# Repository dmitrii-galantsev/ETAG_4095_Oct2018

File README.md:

# ETAG is an RFID reader board used for academic research

Please refer to [Wiki](https://github.com/dmitrii-galantsev/ETAG_Rosvall/wiki) for additional information.

Download files from here [https://github.com/dmitrii-galantsev/ETAG_Rosvall/wiki/Download-Firmware](https://github.com/dmitrii-galantsev/ETAG_Rosvall/wiki/Download-Firmware)

Stable branch: [v1.3](https://github.com/dmitrii-galantsev/ETAG_Rosvall/tree/v1.3)

```
___________________________    ________          .---.        .-----------
\_   _____/\__    ___/  _  \  /  _____/         /     \  __  /    ------
 |    __)_   |    | /  /_\  \/   \  ___        / /     \(  )/    -----
 |        \  |    |/    |    \    \_\  \      //////   ' \/ `   ---
/_______  /  |____|\____|__  /\______  /     //// / // :    : ---
        \/                 \/        \/     // /   /  /`    '--
                                           //          //..\\
                                                  ====UU====UU====
                                                      '//||\\`
                                                         ''``
version: master

Hardware was not created by me, nor were the original files.
Original firmware belongs to Eli Bridge and other collaborators.
Eli's repo: https://github.com/Eli-S-Bridge/ETAG_4095_Oct2018

All work is Licensed in the public domain.

This is a fork highly specialized for Rosvall Lab usage in Indiana University, Bloomington.

*** Directories ***
./ETAG_Rosvall	- Arduino source files. Compile from here.
./board_files	- Board schematics and arduino board file
./images		- Images for the Wiki
./pdfs			- Additional documentation

*** Measurements ***
Date: 	01/08/2018
Power:	Laptop
Commit: 262f8f9e11d535dba44aab24ae57a1ed34d76e22
Comment: these values are strictly for testing and might differ in the field
Stand-by:
	-> 22-35 mA
RFID scanned:
	-> ~40-60 mA
Sleep:
	-> 8.2 mA
```

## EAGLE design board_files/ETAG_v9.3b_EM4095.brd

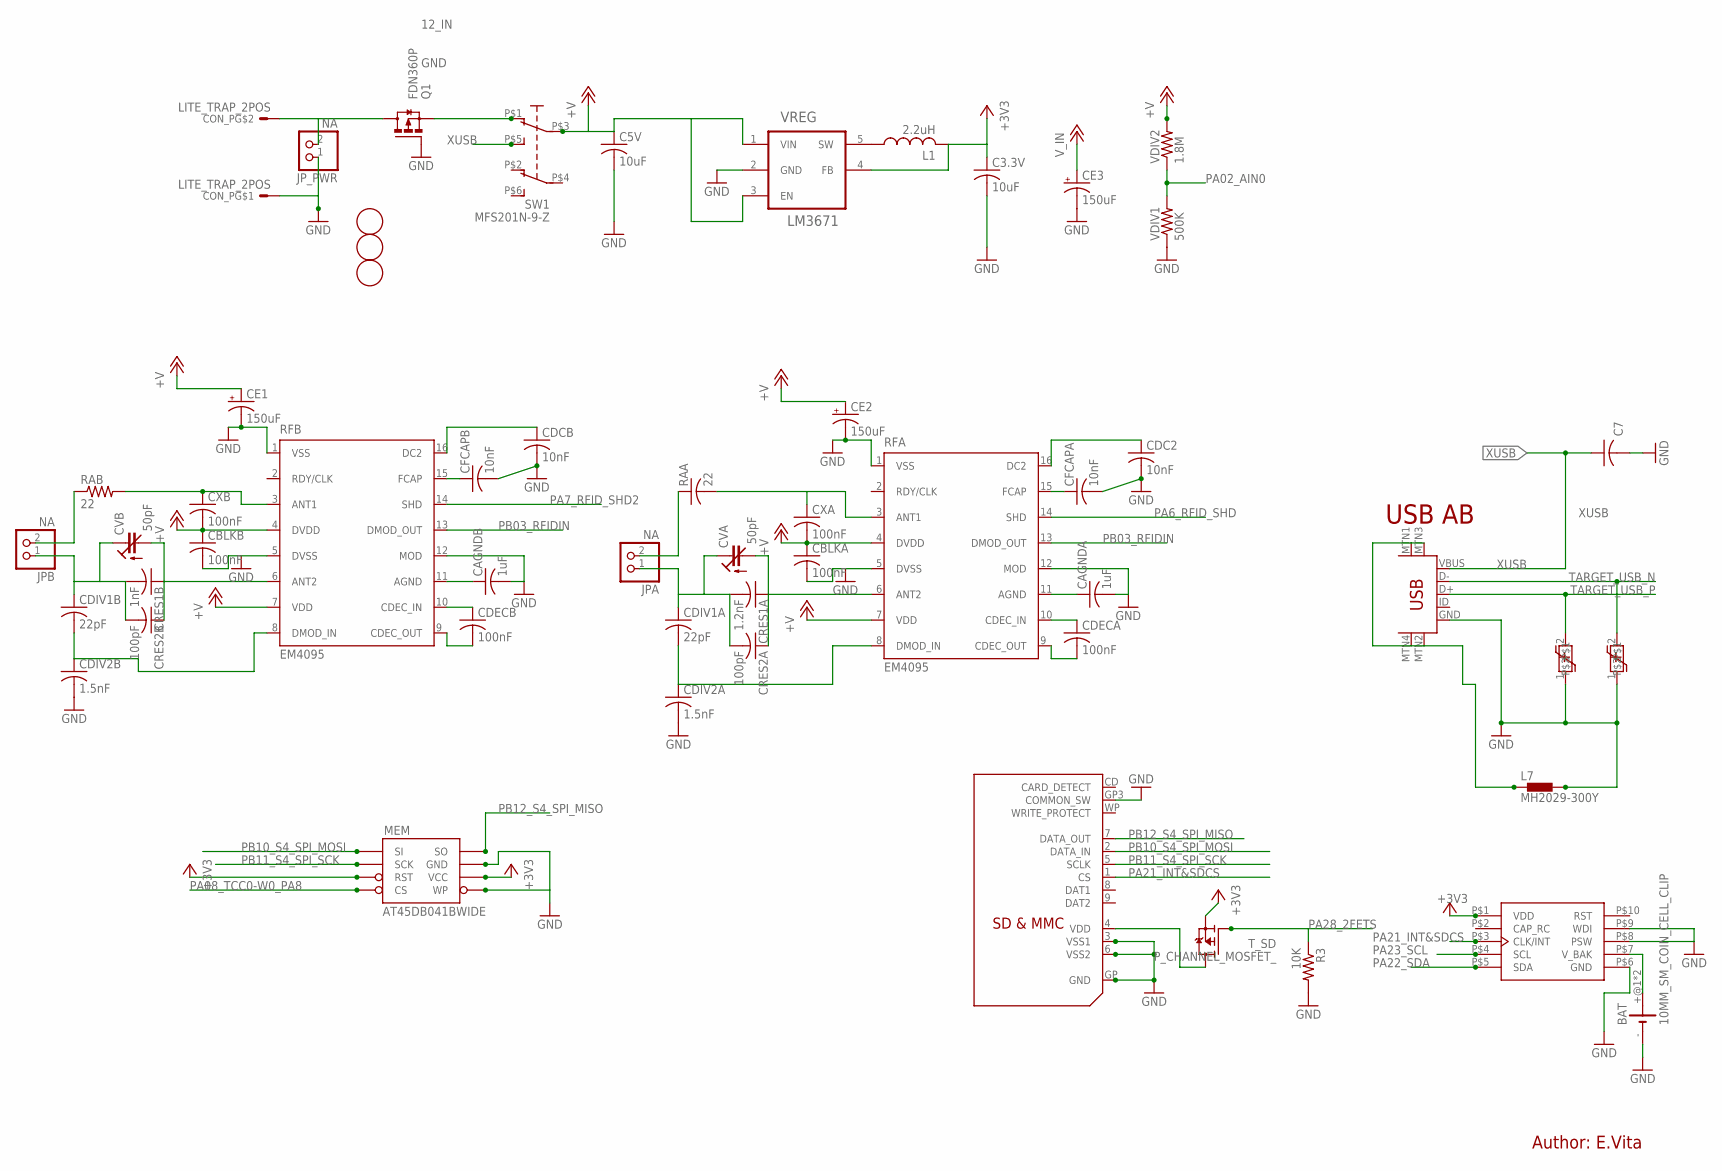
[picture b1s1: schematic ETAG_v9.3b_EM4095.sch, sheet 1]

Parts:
BAT: 10MM_SM_COIN_CELL_CLIP
C3.3V, C5V: 10uF; C0805
C7: 10nF; C0603-ROUND
CAGNDA: 1uF; C0603-ROUND
CAGNDB: 1uF; C0603-ROUND
CBLKA: 100nF; C0603-ROUND
CBLKB: 100nF; C0603-ROUND
CDC2: 10nF; C0603-ROUND
CDCB: 10nF; C0603-ROUND
CDECA: 100nF; C0603-ROUND
CDECB: 100nF; C0603-ROUND
CDIV1A, CDIV1B: 22pF; C0603-ROUND
CDIV2A, CDIV2B: 1.5nF; C0603-ROUND
CE1, CE2, CE3: 150uF; E2-5
CFCAPA: 10nF; C0603-ROUND
CFCAPB: 10nF; C0603-ROUND
CON_P: LITE_TRAP_2POS; LITE_TRAP_MINI
CRES1A: 1.2nF; C0603-ROUND
CRES1B: 1nF; C0603-ROUND
CRES2A, CRES2B: 100pF; C0603-ROUND
CVA: 50pF; CTRIM3018_11
CVB: 50pF; CTRIM3018_11
CXA: 100nF; C0603-ROUND
CXB: 100nF; C0603-ROUND
FD1, FD2, FD3: FIDUCIALMOUNT; FIDUCIA-MOUNT
JPA: NA; 1X02
JPB: NA; 1X02
JP_PWR: NA; 1X02
L1: 2.2uH; SMT_COIL_INDUCTOR_4X4MM
L7: MH2029-300Y; C0805K
MEM: AT45DB041BWIDE; SO08WIDE
Q1: FDN360P; SUPER-SOT3
R3: 10K; C0603-ROUND
RAA: 22; C0805
RAB: 22; R0805
RFA: EM4095; SO16
RFB: EM4095; SO16
RTC: MC-RTC-RV-1805-C3-I2C; MC-RTC-C3
SD: SDMMC06132; 06132
SW1: MFS201N-9-Z
T_SD: P_CHANNEL_MOSFET_; SOT23
USB: USB-MINIB-5PIN; USB-MINIB
VDIV1: 500K; C0603-ROUND
VDIV2: 1.8M; C0603-ROUND
VREG: LM3671; SOT23-5L
Z5, Z6: ESD_SUPRESSOR; C0603-ROUND

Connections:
2GND: L7.1, USB.MTN1 (MTN2), USB.MTN2 (MTN3), USB.MTN3 (MTN1), USB.MTN4
12_IN: CON_P.P$3, CON_P.P$4, JP_PWR.2, Q1.3 (D)
+3V3: C3.3V.1, L1.P$2 (2), MEM.3 (RST), MEM.6 (VCC), RTC.P$1 (VDD), T_SD.2 (S), VREG.4 (FB); also elsewhere on the board
CVB: CDIV1B.1, CRES1B.2, CRES2B.2, CVB.+ (E), JPB.1
GND: BAT.-, C3.3V.2, C5V.2, C7.2, CAGNDA.2, CAGNDB.2, CBLKA.2, CBLKB.2, CDC2.2, CDCB.2, CDIV2A.2, CDIV2B.2, CE1.-, CE2.-, CE3.-, CFCAPA.2, CFCAPB.2, CON_P.P$1, CON_P.P$2, JP_PWR.1, L7.2, MEM.5 (WP), MEM.7 (GND), Q1.1 (G), R3.2, RFA.1 (VSS), RFA.5 (DVSS), RFA.12 (MOD), RFB.1 (VSS), RFB.5 (DVSS), RFB.12 (MOD), RTC.P$6 (GND), RTC.P$8 (PSW), RTC.P$9 (WDI), SD.3 (VSS1), SD.6 (VSS2), SD.GP (GND), SD.GP3 (COMMON_SW), USB.GND, VDIV1.1, VREG.2 (GND), Z5.1, Z6.1; also elsewhere on the board
unnamed: CFCAPB.1, RFB.15 (FCAP)
unnamed: CAGNDB.1, RFB.11 (AGND)
unnamed: CFCAPA.1, RFA.15 (FCAP)
unnamed: CAGNDA.1, RFA.11 (AGND)
unnamed: CDC2.1, RFA.16 (DC2)
unnamed: CRES1B.1, CRES2B.1, CVB.- (A), RFB.6 (ANT2)
unnamed: CDIV1B.2, CDIV2B.1, RFB.8 (DMOD_IN)
unnamed: CDCB.1, RFB.16 (DC2)
unnamed: CDECB.2, RFB.9 (CDEC_OUT)
unnamed: CRES1A.1, CRES2A.1, CVA.- (A), RFA.6 (ANT2)
unnamed: CDIV1A.2, CDIV2A.1, RFA.8 (DMOD_IN)
unnamed: CDIV1A.1, CRES1A.2, CRES2A.2, CVA.+ (E), JPA.1
unnamed: CDECB.1, RFB.10 (CDEC_IN)
unnamed: CXB.1, RAB.2, RFB.3 (ANT1)
unnamed: Q1.2 (S), SW1.P$1 (O)
unnamed: CDECA.2, RFA.9 (CDEC_OUT)
unnamed: CDECA.1, RFA.10 (CDEC_IN)
unnamed: CXA.1, RAA.2, RFA.3 (ANT1)
unnamed: JPB.2, RAB.1
unnamed: JPA.2, RAA.1
PA02_AIN0: VDIV1.2, VDIV2.1; also elsewhere on the board
PA6_RFID_SHD: RFA.14 (SHD); also elsewhere on the board
PA7_RFID_SHD2: RFB.14 (SHD); also elsewhere on the board
PA08_TCC0-W0_PA8: MEM.4 (CS); also elsewhere on the board
PA21_INT&SDCS: RTC.P$3 (CLK/INT), SD.1 (CS); also elsewhere on the board
PA22_SDA: RTC.P$5 (SDA); also elsewhere on the board
PA23_SCL: RTC.P$4 (SCL); also elsewhere on the board
PA28_2FETS: R3.1, T_SD.1 (G); also elsewhere on the board
PB03_RFIDIN: RFA.13 (DMOD_OUT), RFB.13 (DMOD_OUT); also elsewhere on the board
PB10_S4_SPI_MOSI: MEM.1 (SI), SD.2 (DATA_IN); also elsewhere on the board
PB11_S4_SPI_SCK: MEM.2 (SCK), SD.5 (SCLK); also elsewhere on the board
PB12_S4_SPI_MISO: MEM.8 (SO), SD.7 (DATA_OUT); also elsewhere on the board
SW: L1.P$1 (1), VREG.5 (SW)
TARGET_USB_N: USB.D-, Z6.2; also elsewhere on the board
TARGET_USB_P: USB.D+, Z5.2; also elsewhere on the board
VBAT1: BAT.+@1 (+), BAT.+@2 (+), RTC.P$7 (V_BAK)
VDD: SD.4 (VDD), T_SD.3 (D)
V_IN: C5V.1, CBLKA.1, CBLKB.1, CE1.+, CE2.+, CE3.+, CXA.2, CXB.2, RFA.4 (DVDD), RFA.7 (VDD), RFB.4 (DVDD), RFB.7 (VDD), SW1.P$3, VDIV2.2, VREG.1 (VIN), VREG.3 (EN); also elsewhere on the board
XUSB: C7.1, SW1.P$5 (S), USB.VBUS

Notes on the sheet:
USB AB
Author: E.Vita

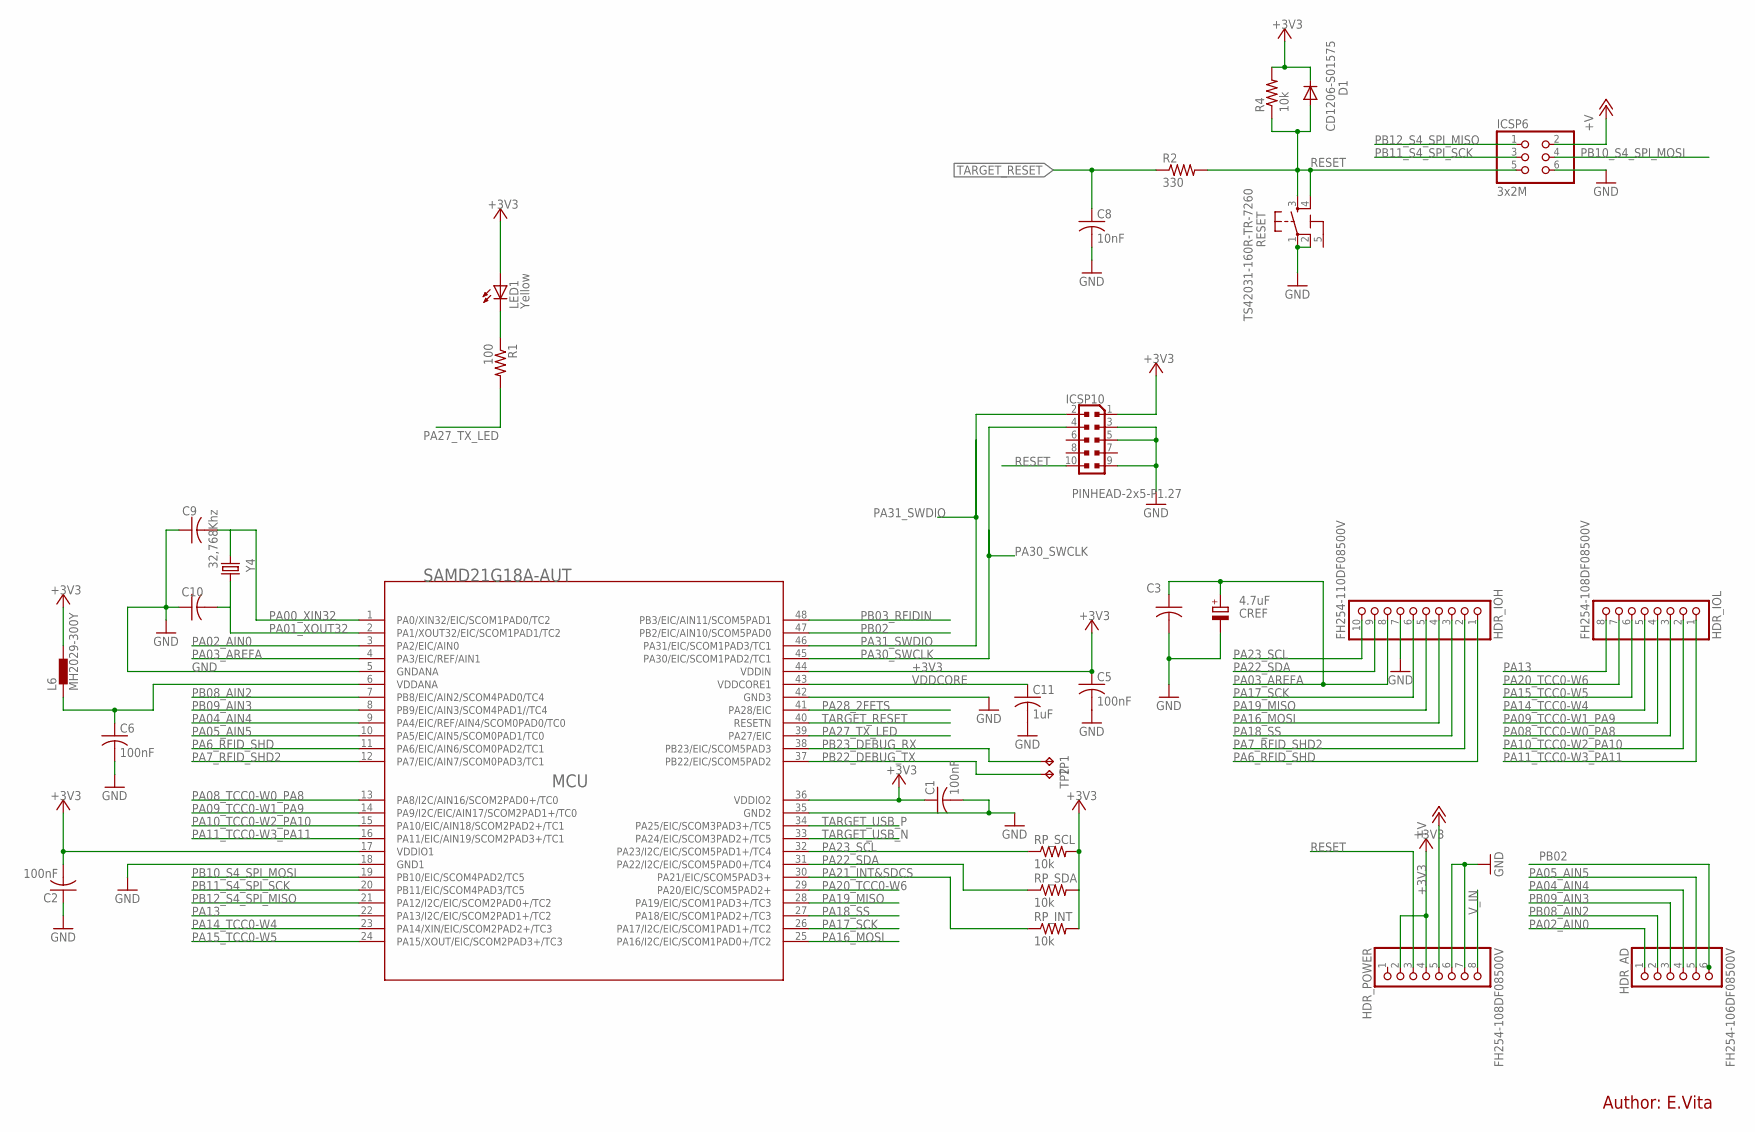
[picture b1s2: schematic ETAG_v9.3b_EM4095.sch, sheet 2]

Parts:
C1, C2, C3, C5, C6: 100nF; C0603-ROUND
C8: 10nF; C0603-ROUND
C9, C10: 22pF; C0603-ROUND
C11: 1uF; C0603-ROUND
CREF: 4.7uF; SMC_A
D1: CD1206-S01575; MINIMELF
HDR_AD: FH254-106DF08500V; 1X06
HDR_IOH: FH254-110DF08500V; 1X10
HDR_IOL: FH254-108DF08500V; 1X08
HDR_POWER: FH254-108DF08500V; 1X08
ICSP6: 3x2M; 2X03
ICSP10: PINHEAD-2x5-P1.27; PINHEAD_2X05_127
L6: MH2029-300Y; C0805K
LED1: Yellow; CHIPLED_0805
MCU: SAMD21G18A-AUT; TQFP48-7X7
R1: 100; C0603-ROUND
R2: 330; C0603-ROUND
R4: 10k; C0603-ROUND
RESET: TS42031-160R-TR-7260; TS42
RP_INT: 10k; C0603-ROUND
RP_SCL: 10k; C0603-ROUND
RP_SDA: 10k; C0603-ROUND
TP1, TP2: TPTP15R; TP15R
Y4: 32,768Khz; RESONATOR_EPSON_FC_145

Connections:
5-GND: RESET.5 (5-GND)
+3V3: C1.1, C2.2, C5.1, D1.C, HDR_POWER.2, HDR_POWER.4, ICSP10.1, L6.2, LED1.A, MCU.17 (VDDIO1), MCU.36 (VDDIO2), MCU.44 (VDDIN), R4.2, RP_INT.2, RP_SCL.2, RP_SDA.2; also elsewhere on the board
GND: C1.2, C2.1, C3.2, C5.2, C6.2, C8.2, C9.1, C10.1, C11.2, CREF.-, HDR_IOH.7, HDR_POWER.6, HDR_POWER.7, ICSP6.6, ICSP10.3, ICSP10.5, ICSP10.9, MCU.5 (GNDANA), MCU.18 (GND1), MCU.35 (GND2), MCU.42 (GND3), RESET.1, RESET.2; also elsewhere on the board
unnamed: LED1.C, R1.1
unnamed: C6.1, L6.1, MCU.6 (VDDANA)
PA00_XIN32: C9.2, MCU.1 (PA0/XIN32/EIC/SCOM1PAD0/TC2), Y4.P$1 (1)
PA01_XOUT32: C10.2, MCU.2 (PA1/XOUT32/EIC/SCOM1PAD1/TC2), Y4.P$2 (2)
PA02_AIN0: HDR_AD.1, MCU.3 (PA2/EIC/AIN0); also elsewhere on the board
PA03_AREFA: C3.1, CREF.+, HDR_IOH.8, MCU.4 (PA3/EIC/REF/AIN1)
PA04_AIN4: HDR_AD.4, MCU.9 (PA4/EIC/REF/AIN4/SCOM0PAD0/TC0)
PA05_AIN5: HDR_AD.5, MCU.10 (PA5/EIC/AIN5/SCOM0PAD1/TC0)
PA6_RFID_SHD: HDR_IOH.1, MCU.11 (PA6/EIC/AIN6/SCOM0PAD2/TC1); also elsewhere on the board
PA7_RFID_SHD2: HDR_IOH.2, MCU.12 (PA7/EIC/AIN7/SCOM0PAD3/TC1); also elsewhere on the board
PA08_TCC0-W0_PA8: HDR_IOL.3, MCU.13 (PA8/I2C/AIN16/SCOM2PAD0+/TC0); also elsewhere on the board
PA09_TCC0-W1_PA9: HDR_IOL.4, MCU.14 (PA9/I2C/EIC/AIN17/SCOM2PAD1+/TC0)
PA10_TCC0-W2_PA10: HDR_IOL.2, MCU.15 (PA10/EIC/AIN18/SCOM2PAD2+/TC1)
PA11_TCC0-W3_PA11: HDR_IOL.1, MCU.16 (PA11/EIC/AIN19/SCOM2PAD3+/TC1)
PA13: HDR_IOL.8, MCU.22 (PA13/I2C/EIC/SCOM2PAD1+/TC2)
PA14_TCC0-W4: HDR_IOL.5, MCU.23 (PA14/XIN/EIC/SCOM2PAD2+/TC3)
PA15_TCC0-W5: HDR_IOL.6, MCU.24 (PA15/XOUT/EIC/SCOM2PAD3+/TC3)
PA16_MOSI: HDR_IOH.4, MCU.25 (PA16/I2C/EIC/SCOM1PAD0+/TC2)
PA17_SCK: HDR_IOH.6, MCU.26 (PA17/I2C/EIC/SCOM1PAD1+/TC2)
PA18_SS: HDR_IOH.3, MCU.27 (PA18/EIC/SCOM1PAD2+/TC3)
PA19_MISO: HDR_IOH.5, MCU.28 (PA19/EIC/SCOM1PAD3+/TC3)
PA20_TCC0-W6: HDR_IOL.7, MCU.29 (PA20/EIC/SCOM5PAD2+)
PA21_INT&SDCS: MCU.30 (PA21/EIC/SCOM5PAD3+), RP_INT.1; also elsewhere on the board
PA22_SDA: HDR_IOH.9, MCU.31 (PA22/I2C/EIC/SCOM5PAD0+/TC4), RP_SDA.1; also elsewhere on the board
PA23_SCL: HDR_IOH.10, MCU.32 (PA23/I2C/EIC/SCOM5PAD1+/TC4), RP_SCL.1; also elsewhere on the board
PA27_TX_LED: MCU.39 (PA27/EIC), R1.2
PA28_2FETS: MCU.41 (PA28/EIC); also elsewhere on the board
PA30_SWCLK: ICSP10.4, MCU.45 (PA30/EIC/SCOM1PAD2/TC1)
PA31_SWDIO: ICSP10.2, MCU.46 (PA31/EIC/SCOM1PAD3/TC1)
PB02: HDR_AD.6, MCU.47 (PB2/EIC/AIN10/SCOM5PAD0)
PB03_RFIDIN: MCU.48 (PB3/EIC/AIN11/SCOM5PAD1); also elsewhere on the board
PB08_AIN2: HDR_AD.2, MCU.7 (PB8/EIC/AIN2/SCOM4PAD0/TC4)
PB09_AIN3: HDR_AD.3, MCU.8 (PB9/EIC/AIN3/SCOM4PAD1//TC4)
PB10_S4_SPI_MOSI: ICSP6.4, MCU.19 (PB10/EIC/SCOM4PAD2/TC5); also elsewhere on the board
PB11_S4_SPI_SCK: ICSP6.3, MCU.20 (PB11/EIC/SCOM4PAD3/TC5); also elsewhere on the board
PB12_S4_SPI_MISO: ICSP6.1, MCU.21 (PA12/I2C/EIC/SCOM2PAD0+/TC2); also elsewhere on the board
PB22_DEBUG_TX: MCU.37 (PB22/EIC/SCOM5PAD2), TP2.TP
PB23_DEBUG_RX: MCU.38 (PB23/EIC/SCOM5PAD3), TP1.TP
RESET: D1.A, HDR_POWER.3, ICSP6.5, ICSP10.10, R2.2, R4.1, RESET.3, RESET.4
TARGET_RESET: C8.1, MCU.40 (RESETN), R2.1
TARGET_USB_N: MCU.33 (PA24/EIC/SCOM3PAD2+/TC5); also elsewhere on the board
TARGET_USB_P: MCU.34 (PA25/EIC/SCOM3PAD3+/TC5); also elsewhere on the board
VDDCORE: C11.1, MCU.43 (VDDCORE1)
V_IN: HDR_POWER.5, HDR_POWER.8, ICSP6.2; also elsewhere on the board

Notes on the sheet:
Author: E.Vita

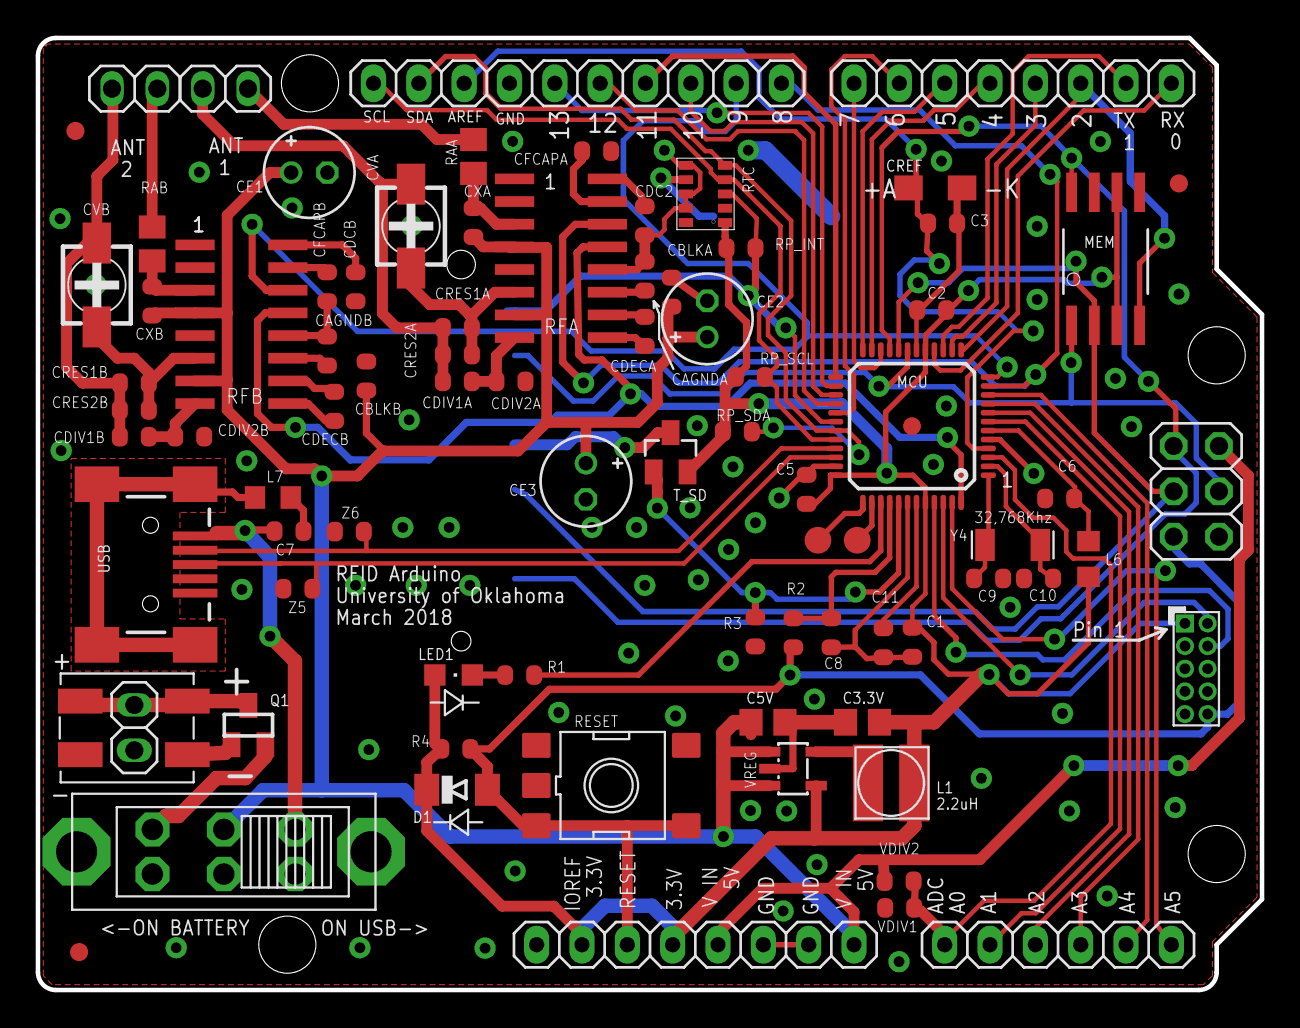
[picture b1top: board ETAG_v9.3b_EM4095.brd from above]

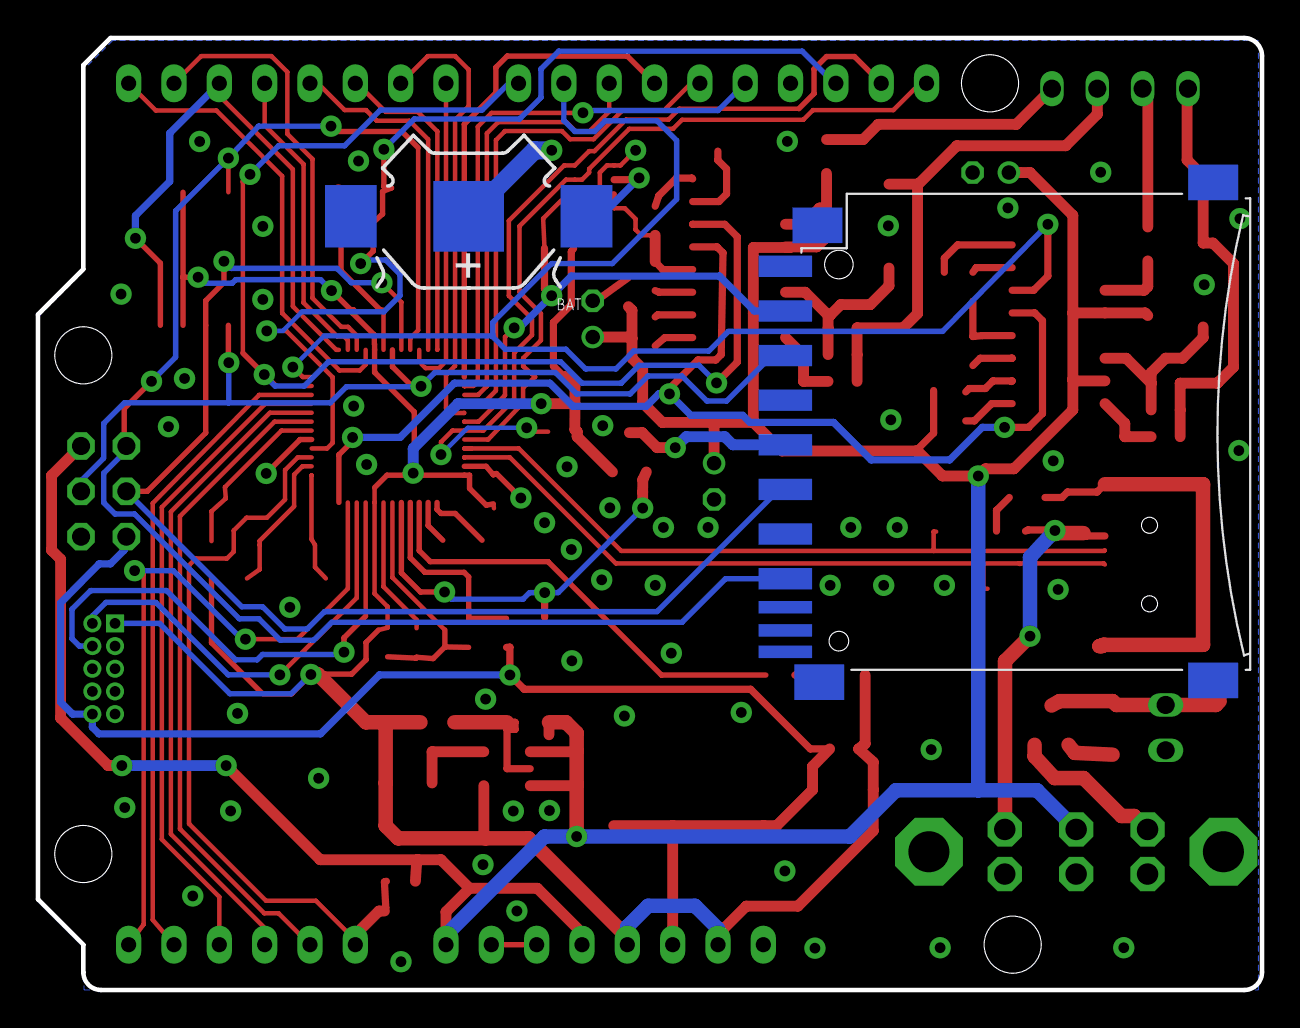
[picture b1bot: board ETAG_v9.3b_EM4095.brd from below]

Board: 4 copper layers, 68.6 x 53.3 mm, 85 parts (2 on the bottom side), 73 nets.

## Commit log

2018-11-10 update comments
2019-01-09 add README
2019-01-09 add measurements
2019-01-09 correct misspelling
2019-01-09 add images
2019-01-10 add board id
2019-01-11 clean up and remove sleep in the loop
2019-01-12 add logging, move const
2019-01-14 sd card format, board ID and cleanup
2019-01-14 add more docs images
2019-01-16 add logo, version, clean up tests and header file
2019-01-23 organize the directories
2019-01-25 change poll time name
2019-01-25 improve error messages
2019-01-25 add v1.2 archive
2019-01-25 add archives
2019-01-25 hotfix
2019-01-25 hotfix and delete archives
2019-01-25 hotfix for v1.2
2019-01-28 add sleep
2019-01-29 latest update
2019-02-06 update header file
2019-02-11 don't ask user input when connected to battery
2019-02-18 update scanning parameters to be consistent with gen2s
2019-03-13 stable version update
2020-02-02 ETAG board files updated, CS pin must be changed

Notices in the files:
parts and their libraries:
SparkFun-DigitalIC: Licensing: Creative Commons ShareAlike 4.0 International - https://creativecommons.org/licenses/by-sa/4.0
